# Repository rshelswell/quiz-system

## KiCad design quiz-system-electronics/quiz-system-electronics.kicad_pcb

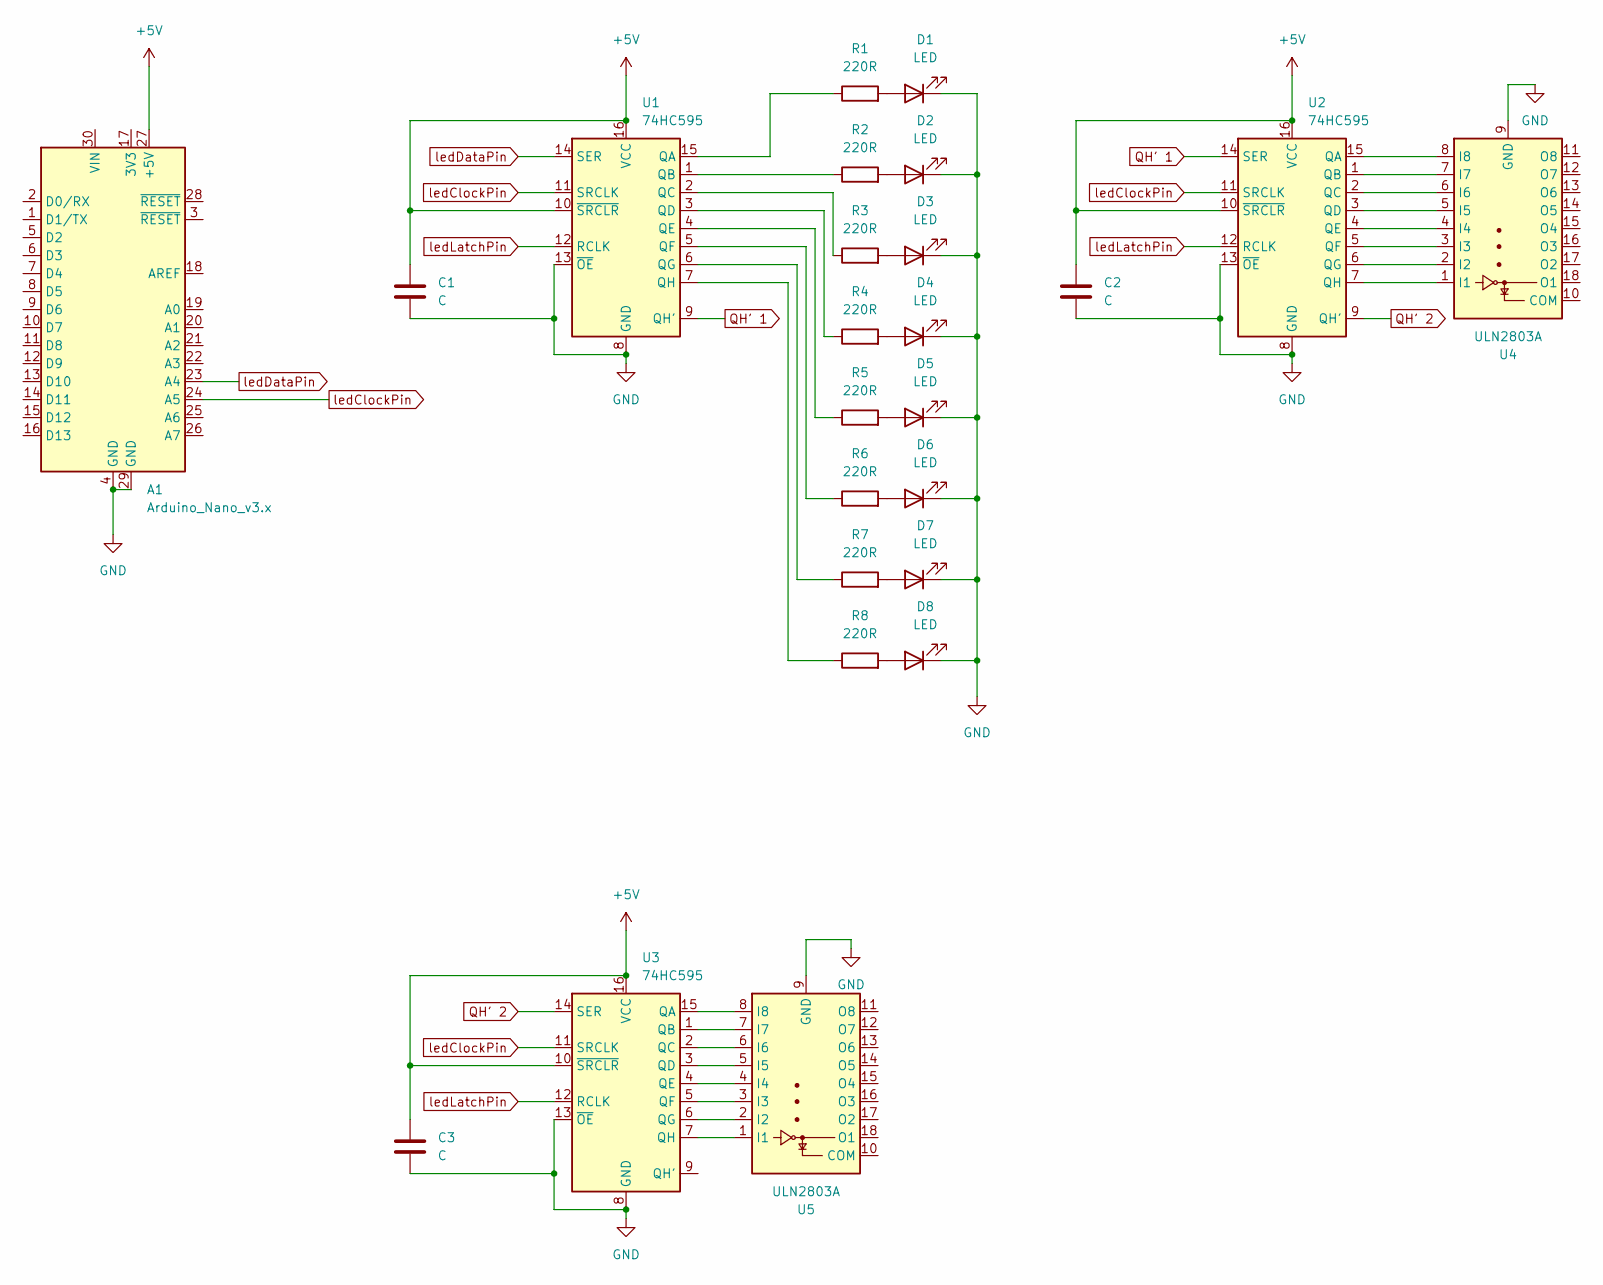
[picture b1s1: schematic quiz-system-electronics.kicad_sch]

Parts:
A1: Arduino_Nano_v3.x; Arduino_Nano_WithMountingHoles
C1, C2, C3: C; C_0805_2012Metric
D1, D2, D3, D4, D5, D6, D7, D8: LED; LED_2010_5025Metric
R1, R2, R3, R4, R5, R6, R7, R8: 220R; R_0815_2038Metric
U1, U2, U3: 74HC595; DIP-16_W7.62mm_SMDSocket_SmallPads
U4, U5: ULN2803A; DIP-18_W7.62mm_SMDSocket_SmallPads

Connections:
+5V: A1.27 (+5V), C1.1, C2.1, C3.1, U1.10 (~SRCLR), U1.16 (VCC), U2.10 (~SRCLR), U2.16 (VCC), U3.10 (~SRCLR), U3.16 (VCC)
GND: A1.4 (GND), A1.29 (GND), C1.2, C2.2, C3.2, D1.1 (K), D2.1 (K), D3.1 (K), D4.1 (K), D5.1 (K), D6.1 (K), D7.1 (K), D8.1 (K), U1.8 (GND), U1.13 (~OE), U2.8 (GND), U2.13 (~OE), U3.8 (GND), U3.13 (~OE), U4.9 (GND), U5.9 (GND)
unnamed: D1.2 (A), R1.2
unnamed: D2.2 (A), R2.2
unnamed: D3.2 (A), R3.2
unnamed: D4.2 (A), R4.2
unnamed: D5.2 (A), R5.2
unnamed: D6.2 (A), R6.2
unnamed: D7.2 (A), R7.2
unnamed: D8.2 (A), R8.2
unnamed: R1.1, U1.15 (QA)
unnamed: R2.1, U1.1 (QB)
unnamed: R3.1, U1.2 (QC)
unnamed: R4.1, U1.3 (QD)
unnamed: R5.1, U1.4 (QE)
unnamed: R6.1, U1.5 (QF)
unnamed: R7.1, U1.6 (QG)
unnamed: R8.1, U1.7 (QH)
unnamed: U2.15 (QA), U4.8 (I8)
unnamed: U2.1 (QB), U4.7 (I7)
unnamed: U2.2 (QC), U4.6 (I6)
unnamed: U2.3 (QD), U4.5 (I5)
unnamed: U2.4 (QE), U4.4 (I4)
unnamed: U2.5 (QF), U4.3 (I3)
unnamed: U2.6 (QG), U4.2 (I2)
unnamed: U2.7 (QH), U4.1 (I1)
unnamed: U3.15 (QA), U5.8 (I8)
unnamed: U3.1 (QB), U5.7 (I7)
unnamed: U3.2 (QC), U5.6 (I6)
unnamed: U3.3 (QD), U5.5 (I5)
unnamed: U3.4 (QE), U5.4 (I4)
unnamed: U3.5 (QF), U5.3 (I3)
unnamed: U3.6 (QG), U5.2 (I2)
unnamed: U3.7 (QH), U5.1 (I1)
QH' 1: U1.9 (QH'), U2.14 (SER)
QH' 2: U2.9 (QH'), U3.14 (SER)
ledClockPin: A1.24 (A5), U1.11 (SRCLK), U2.11 (SRCLK), U3.11 (SRCLK)
ledDataPin: A1.23 (A4), U1.14 (SER)
ledLatchPin: U1.12 (RCLK), U2.12 (RCLK), U3.12 (RCLK)

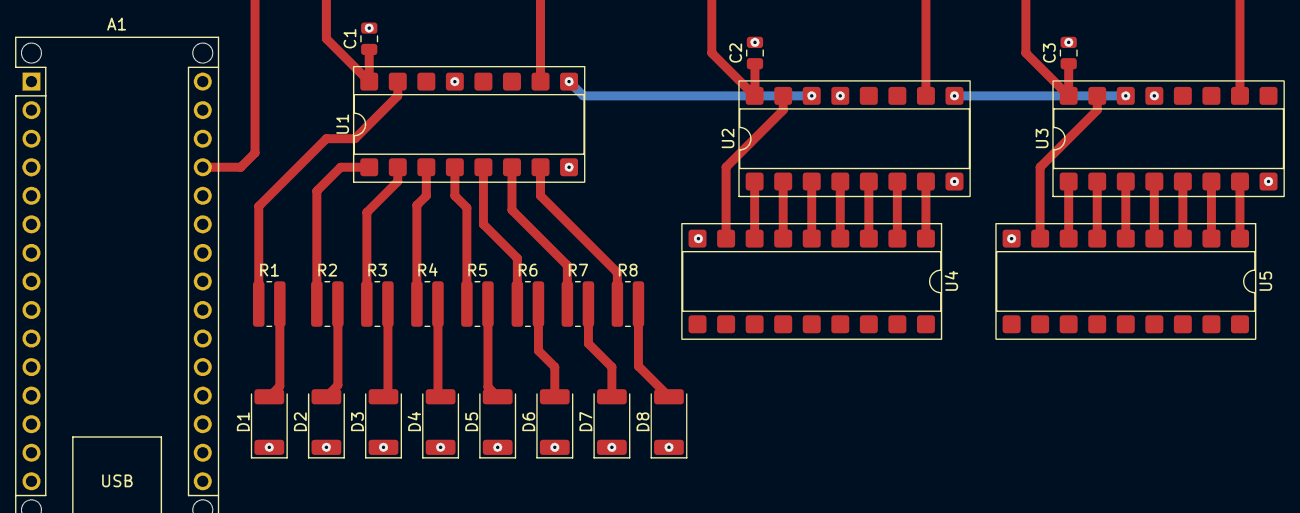
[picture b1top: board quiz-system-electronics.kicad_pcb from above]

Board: 2 copper layers, 25 parts (0 on the bottom side), 39 nets.

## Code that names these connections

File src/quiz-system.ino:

#include <Bounce2.h>
#include <LedControl.h>

const int buttonPin1 = 9;
const int buttonPin2 = 8;
const int buttonPin3 = 7;
const int buttonPin4 = 6;
const int buttonPin5 = 5;
const int buttonPin6 = 4;
const int buttonPin7 = 3;
const int buttonPin8 = 2;
const int buttonPin10p = 14;
const int buttonPinm5p = 15;
const int buttonPin5p = 16;
const int buttonPinNQ = 17;

const int scoreLatchPin = 10;
const int scoreDataPin = 11;
const int scoreClockPin = 13;

const int ledLatchPin = 1;
const int ledDataPin = 18;
const int ledClockPin = 19;

bool answered = false;
int activePlayer = 0;
int team1Score = 0;
int team2Score = 0;
int debounceDelay = 20;
float timer = 0;

LedControl lsScore=LedControl(scoreDataPin, scoreClockPin, scoreLatchPin, 1);

Bounce2::Button button1 = Bounce2::Button();
Bounce2::Button button2 = Bounce2::Button();
Bounce2::Button button3 = Bounce2::Button();
Bounce2::Button button4 = Bounce2::Button();
Bounce2::Button button5 = Bounce2::Button();
Bounce2::Button button6 = Bounce2::Button();
Bounce2::Button button7 = Bounce2::Button();
Bounce2::Button button8 = Bounce2::Button();
Bounce2::Button button10p = Bounce2::Button();
Bounce2::Button button5p = Bounce2::Button();
Bounce2::Button buttonm5p = Bounce2::Button();
Bounce2::Button buttonNQ = Bounce2::Button();

void setup() {
  pinMode(scoreLatchPin, OUTPUT);
  pinMode(scoreDataPin, OUTPUT);
  pinMode(scoreClockPin, OUTPUT);
  pinMode(ledLatchPin, OUTPUT);
  pinMode(ledDataPin, OUTPUT);
  pinMode(ledClockPin, OUTPUT);

  updateLights();

  /*
   The MAX72XX is in power-saving mode on startup,
   we have to do a wakeup call
   */
  lsScore.shutdown(0,false);
  /* Set the brightness to a medium values */
  lsScore.setIntensity(0,8);
  /* and clear the display */
  lsScore.clearDisplay(0);

  updateScoreDisplay();
  
  /*
   Set up the button objects.
   8 player buttons using external pull-down resistors
   */
  button1.attach(buttonPin1, INPUT_PULLUP);
  button1.interval(debounceDelay);
  button1.setPressedState(LOW);

  button2.attach(buttonPin2, INPUT_PULLUP);
  button2.interval(debounceDelay);
  button2.setPressedState(LOW);

  button3.attach(buttonPin3, INPUT_PULLUP);
  button3.interval(debounceDelay);
  button3.setPressedState(LOW);

  button4.attach(buttonPin4, INPUT_PULLUP);
  button4.interval(debounceDelay);
  button4.setPressedState(LOW);

  button5.attach(buttonPin5, INPUT_PULLUP);
  button5.interval(debounceDelay);
  button5.setPressedState(LOW);

  button6.attach(buttonPin6, INPUT_PULLUP);
  button6.interval(debounceDelay);
  button6.setPressedState(LOW);

  button7.attach(buttonPin7, INPUT_PULLUP);
  button7.interval(debounceDelay);
  button7.setPressedState(LOW);

  button8.attach(buttonPin8, INPUT_PULLUP);
  button8.interval(debounceDelay);
  button8.setPressedState(LOW);

  /*
   Set up the score increment and next question buttons.
   4 buttons using the internal pull-up resistor
  */
  button10p.attach(buttonPin10p, INPUT_PULLUP);
  button10p.interval(debounceDelay);
  button10p.setPressedState(LOW);

  button5p.attach(buttonPin5p, INPUT_PULLUP);
  button5p.interval(debounceDelay);
  button5p.setPressedState(LOW);

  buttonm5p.attach(buttonPinm5p, INPUT_PULLUP);
  buttonm5p.interval(debounceDelay);
  buttonm5p.setPressedState(LOW);

  buttonNQ.attach(buttonPinNQ, INPUT_PULLUP);
  buttonNQ.interval(debounceDelay);
  buttonNQ.setPressedState(LOW);

}

void loop() {
  if (answered) {
    changeScore();
    checkNextQuestionButton();
  } else {
    checkPlayerButtons();
  }
  updateLights();
}


void checkPlayerButtons() {
  button1.update();
  button2.update();
  button3.update();
  button4.update();
  button5.update();
  button6.update();
  button7.update();
  button8.update();
  if ( button1.pressed() ) {
    answered = true;
    activePlayer = 1;
    return;
  } else if ( button2.pressed() ) {
    answered = true;
    activePlayer = 2;
    return;
  } else if ( button3.pressed() ) {
    answered = true;
    activePlayer = 3;
    return;
  } else if ( button4.pressed() ) {
    answered = true;
    activePlayer = 4;
    return;
  } else if ( button5.pressed() ) {
    answered = true;
    activePlayer = 5;
    return;
  } else if ( button6.pressed() ) {
    answered = true;
    activePlayer = 6;
    return;
  } else if ( button7.pressed() ) {
    answered = true;
    activePlayer = 7;
    return;
  } else if ( button8.pressed() ) {
    answered = true;
    activePlayer = 8;
    return;
  } 
}

void checkNextQuestionButton() {
  buttonNQ.update();
  
  if (buttonNQ.pressed()) {
    answered = false;
    activePlayer = 0;
  }
}

void changeScore() {
  button10p.update();
  button5p.update();
  buttonm5p.update();
  int deltaScore = 0;
  if (button10p.pressed()) {
    deltaScore = 10;
  } else if (button5p.pressed()) {
    deltaScore = 5;
  } else if (buttonm5p.pressed()) {
    deltaScore = -5;
  }
  if (deltaScore != 0) {
    switch (activePlayer) {
      case 1:
      case 2:
      case 3:
      case 4:
        team1Score += deltaScore;
        updateScoreDisplay();
        break;
      case 5:
      case 6:
      case 7:
      case 8:
        team2Score += deltaScore;
        updateScoreDisplay();
        break;
      default:
        return;
    }
  }
}

void displayNumber3(int value, int startDigit) {
  // Convert to string
  char buf[5];
  sprintf(buf, "%4d", value);   // produces right‑aligned: "  45", " 123", " -45"
  // Write characters into 3 digits
  for (int i = 0; i < 3; i++) {
    char c = buf[1 + i];  // use last 3 positions
    int digit = startDigit - (2 - i);
    
    if (c == ' ') {
      lsScore.setChar(0, digit, ' ', false);
    } else if (c == '-') {
      // Display minus sign
      lsScore.setChar(0, digit, '-', false);
    } else {
      lsScore.setDigit(0, digit, c - '0', false);
    }
  }
}

void updateScoreDisplay() {
  displayNumber3(team1Score, 2);
  displayNumber3(team2Score, 5);
}

void updateLights() {
  if (!answered) {
    digitalWrite(ledLatchPin, LOW);
    shiftOut(ledDataPin, ledClockPin, MSBFIRST, 0b00000000);
    shiftOut(ledDataPin, ledClockPin, MSBFIRST, 0b00000000);
    shiftOut(ledDataPin, ledClockPin, MSBFIRST, 0b00000000);
    digitalWrite(ledLatchPin, HIGH);
  } else {
    digitalWrite(ledLatchPin, LOW);
    shiftOut(ledDataPin, ledClockPin, MSBFIRST, 1 << (activePlayer - 1));
    shiftOut(ledDataPin, ledClockPin, MSBFIRST, 1 << (activePlayer - 1));
    shiftOut(ledDataPin, ledClockPin, MSBFIRST, 1 << (activePlayer < 5 ? 0 : 1));
    digitalWrite(ledLatchPin, HIGH);
  }
}

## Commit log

2026-03-10 add README to inital commit
2026-03-10 added current working .ino file for Arduino Nano
2026-03-10 added initial schematic and PCB layout in KiCad files
2026-03-14 Updated schematic and started to connect PCB
2026-03-14 added .zip files to .gitignore
